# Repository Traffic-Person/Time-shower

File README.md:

# Time-shower
A time shower consisting of a oled display 2 buttons a raspberry pi pico and 4 leds :) See [Bom](Bom.csv)

# Schematics

# Pcb

(mounting holes so i can mount it to whatever i want)

# Case
No case i have decided to make it be able to mount anywhere! Plastic, Cardboard, metal you name it and i also like the look of bare electronics

# Pcb Render

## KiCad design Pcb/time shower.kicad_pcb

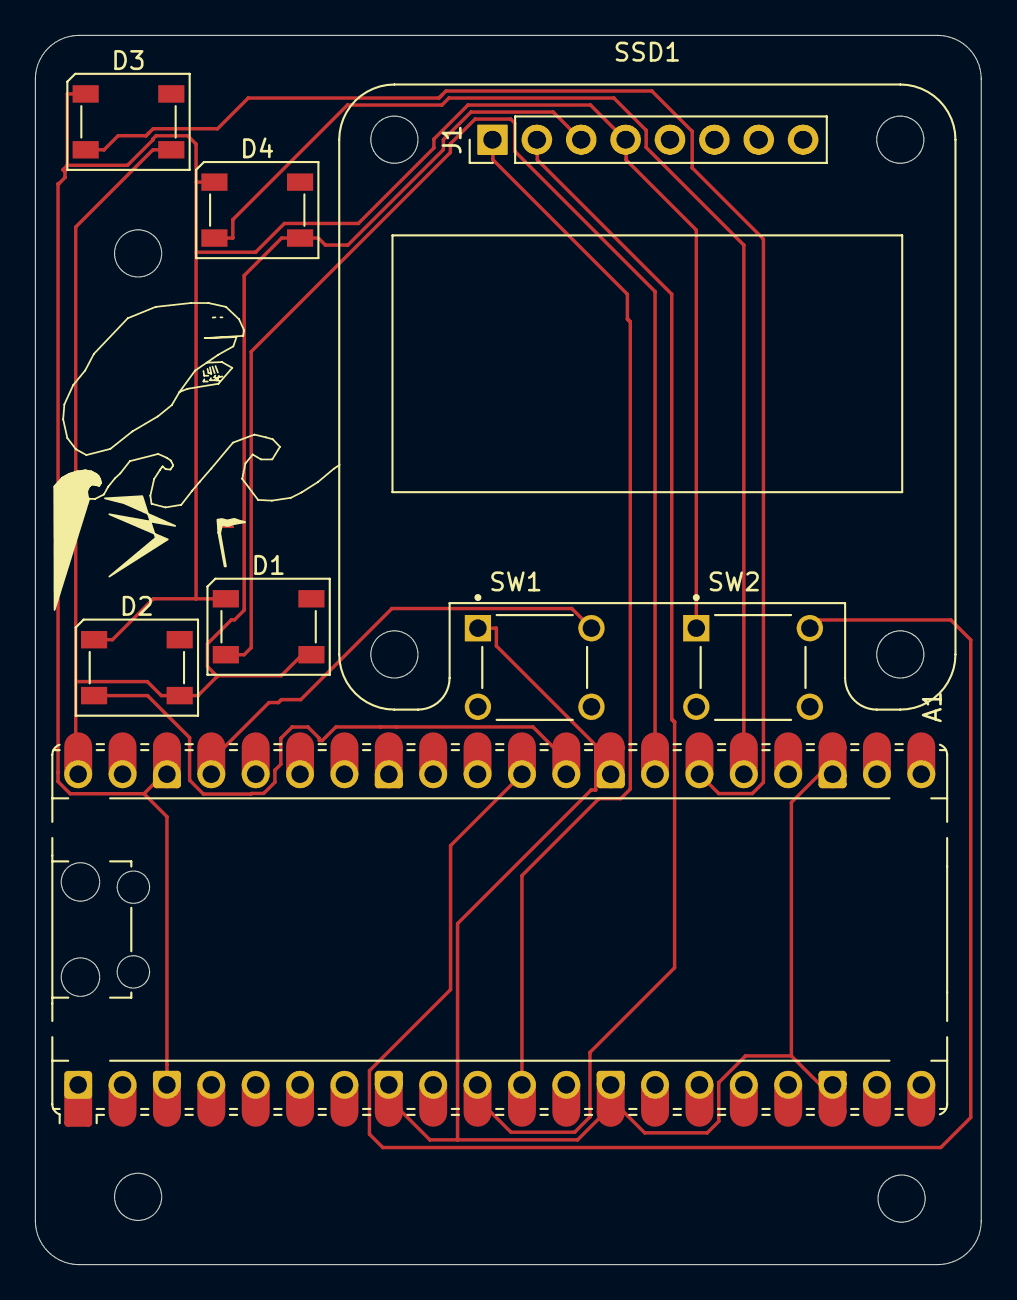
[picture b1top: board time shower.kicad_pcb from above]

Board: 2 copper layers, 54.1 x 70.4 mm, 9 parts (0 on the bottom side), 8 nets.

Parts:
A1: RaspberryPi_Pico; RaspberryPi_Pico_Common_Unspecified
D1, D2, D3, D4: SK6812; LED_SK6812_PLCC4_5.0x5.0mm_P3.2mm
J1: Conn_01x08_Pin; PinHeader_1x08_P2.54mm_Vertical
SSD1: Adafruit_SSD1306
SW1, SW2: SW_Push; SW_TS02-66-70-BK-100-LCR-D

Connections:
+5V: A1.40 (VBUS), D1.3 (VDD), D2.3 (VDD), D3.3 (VDD), D4.3 (VDD), J1.3, SSD1.3 (VCC)
GND: A1.3 (GND), A1.8 (GND), A1.13 (GND), A1.18 (GND), A1.23 (GND), A1.28 (GND), A1.38 (GND), D1.1 (VSS), D2.1 (VSS), D3.1 (VSS), D4.1 (VSS), J1.4, SSD1.4 (GND), SW1.1, SW2.1
unnamed: A1.37 (3V3_EN), SW1.2
unnamed: A1.10 (GPIO7), J1.2, SSD1.2 (SCL)
unnamed: A1.11 (GPIO8), J1.1, SSD1.1 (SDA)
unnamed: A1.27 (GPIO21), D1.2 (DIN)
unnamed: A1.29 (GPIO22), D2.2 (DIN)
unnamed: A1.30 (RUN), SW2.2

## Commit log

2025-12-07 Update README with project details and images
    Added project description, schematics, PCB, and case information.
2025-12-07 Fix capitalization in BOM reference
2025-12-07 Add new components to Bom.csv with cost details
2025-12-07 Add total cost line to Bom.csv
    Add total cost summary to the bill of materials.
2025-12-07 Fix typo in total line of Bom.csv
2025-12-07 Update Bom.csv with new items and total
    Added screws and nuts to the bill of materials and updated total.
2025-12-07 Add time display with OLED and LED indicators
    This script initializes an OLED display and SK6812 LEDs to show the current time and indicate seconds with color changes.
2025-12-07 Add PCB render section to README
    Added PCB render image to the README.
2025-12-07 Add image to Pcb section in README
    Added an additional image to the Pcb section of the README.
